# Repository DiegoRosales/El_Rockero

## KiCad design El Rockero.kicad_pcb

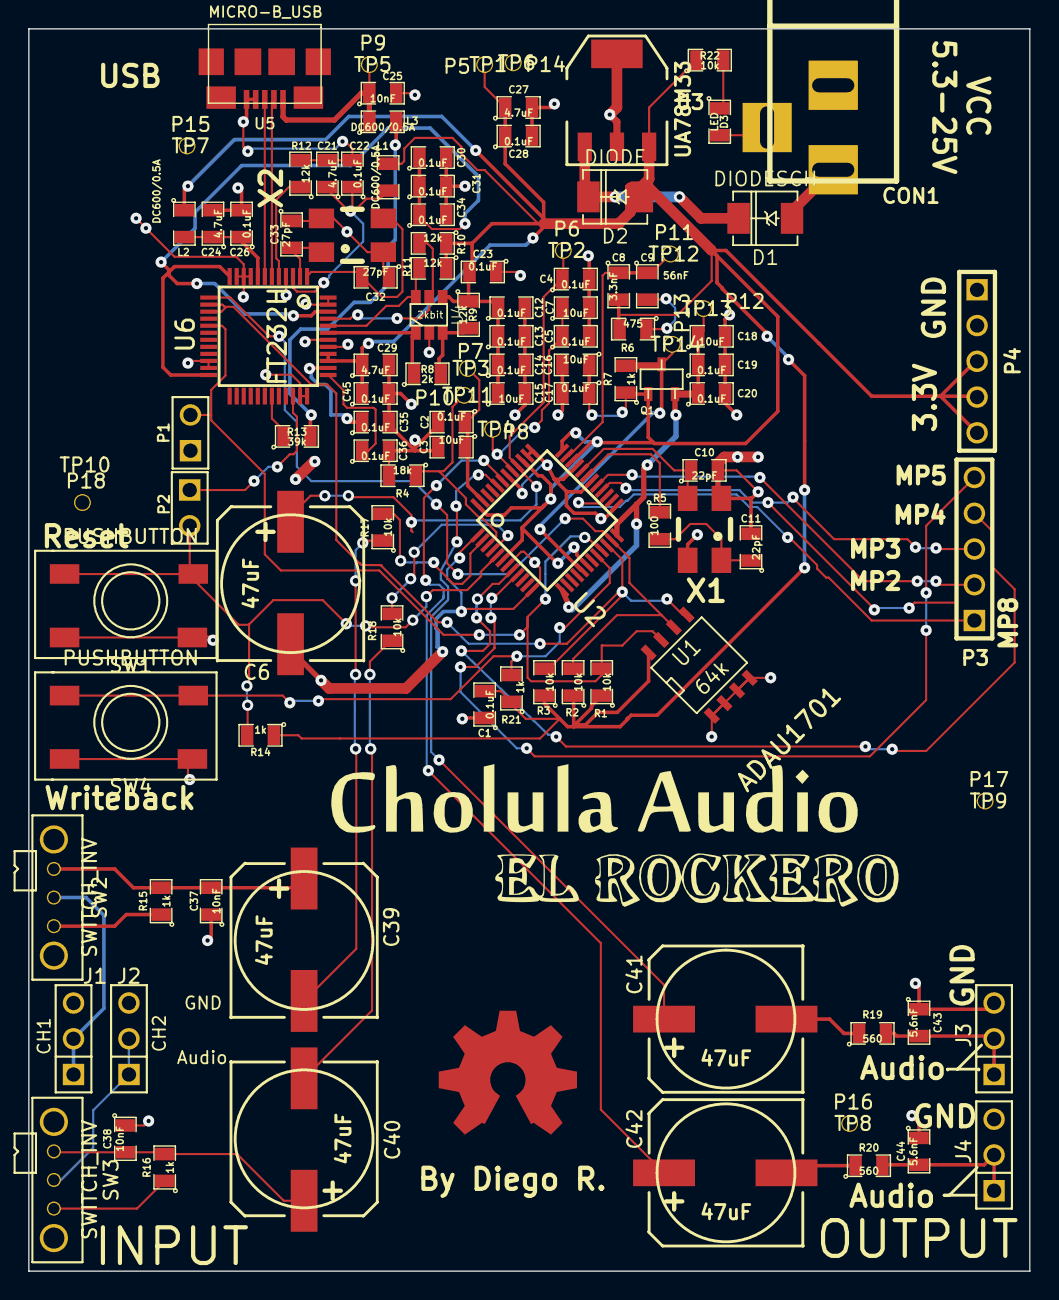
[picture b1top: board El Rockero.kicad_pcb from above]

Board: 2 copper layers, 71.1 x 88.3 mm, 110 parts (0 on the bottom side), 60 nets.

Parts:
C1, C2, C4, C5, C12, C13, C14, C17, C19, C20, C22, C23, C26, C28, C30, C31, C34, C35, C36, C45: 0.1uF; SM0805
C3, C7, C15, C16, C18: 10uF; SM0805
C6, C39, C40, C41, C42: 47uF; SMDSVP10
C8: 3.3nF; SM0805
C9: 56nF; SM0805
C10, C11: 22pF; SM0805
C21, C24, C27, C29: 4.7uF; SM0805
C25, C37, C38: 10nF; SM0805
C32, C33: 27pF; SM0805
C43, C44: 5.6nF; SM0805
CON1: BARREL_JACK
D1: DIODESCH; DO-214AC(SMA)
D2: DIODE; DO-214AC(SMA)
D3: LED; SM0805
J1: IN_L; PIN_ARRAY_3X1
J2: IN_R; PIN_ARRAY_3X1
J3: OUT_L; PIN_ARRAY_3X1
J4: OUT_R; PIN_ARRAY_3X1
L1, L2, L3: DC600/0.5A; SM0805
OSHW_COPPER_10MM: VAL**; OSHW_COPPER_10MM
P1: WP_Jumper; PIN_ARRAY_2X1
P2: USB_RST_JPR; PIN_ARRAY_2X1
P3, P4: CONN_5; PIN_ARRAY_5x1
P5: TP1; TP
P6: TP2; TP
P7: TP3; TP
P8: TP4; TP
P9: TP5; TP
P10: TP11; TP
P11: TP12; TP
P12: TP13; TP
P13: TP14; TP
P14: TP6; TP
P15: TP7; TP
P16: TP8; TP
P17: TP9; TP
P18: TP10; TP
Q1: ZXTP25040DFHTA; sot23
R1, R2, R3, R17, R18, R22: 10k; SM0805
R4: 18k; SM0805
R5: 100; SM0805
R6: 475; SM0805
R7, R14, R15, R16, R21: 1k; SM0805
R8: 2k; SM0805
R9, R10, R11, R12: 12k; SM0805
R13: 39k; SM0805
R19, R20: 560; SM0805
SW1, SW4: PUSHBUTTON
SW2, SW3: SWITCH_INV; SPDT Switch
U1: 64k; SO8N
U2: ADAU1701; LQFP48
U3: UA78M33
U4: 2kbit; SOT23_6
U5: MICRO-B_USB
U6: FT232H; LQFP48
X1, X2: CRYSTAL_4PIN; Crystal_SMD_0603_4Pads_RevA_09Aug2010

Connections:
+9V: CON1.1, D1.1
AVDD/PVDD (3.3v): C1.2, C8.2, C12.1, C13.1, C14.1, C15.1, C16.1, C17.1, C23.2, C27.1, C28.1, C29.1, C45.1, D2.1, L1.1, L2.1, P4.3, P4.4, P4.5, P5.1, Q1.1, R1.1, R2.1, R3.1, R6.2, R7.1, R9.1, R10.1, R11.1, R14.1, R21.1, R22.1, U1.8, U2.6, U2.18, U2.34, U2.36, U2.39, U2.48, U3.3, U4.4, U6.39, U6.40
DAC2: C41.1, U2.44
DAC3: C42.1, U2.43
DVDD: C18.1, C19.1, C20.1, P12.1, Q1.3, U2.13, U2.24
EECLK: R11.2, U4.6, U6.44
EECS: R10.2, U4.5, U6.45
EEDATA: R8.1, U4.1, U6.43
GND: C1.1, C2.2, C3.2, C4.2, C5.2, C6.2, C7.2, C10.2, C11.2, C12.2, C13.2, C14.2, C15.2, C16.2, C17.2, C18.2, C19.2, C20.2, C21.2, C22.2, C23.1, C24.2, C25.2, C26.2, C27.2, C28.2, C29.2, C30.2, C31.2, C32.1, C33.1, C34.2, C35.2, C36.2, C37.1, C38.1, C43.1, C44.1, C45.2, CON1.2, CON1.3, D3.2, J1.3, J2.3, J3.3, J4.3, P1.1, P4.1, P4.2, P14.1, P15.1, P16.1, P17.1, P18.1, R4.2, R12.2, SW1.1, SW1.2, SW4.1, SW4.2, U1.1, U1.2, U1.3, U1.4, U2.1, U2.7, U2.12, U2.25, U2.30, U2.33, U2.37, U2.38, U2.42, U3.2, U4.2, U5.4, U5.5, U6.4, U6.9, U6.10, U6.11, U6.22, U6.23, U6.35, U6.36, U6.41, U6.42, U6.47, U6.48, X1.2, X1.4, X2.2, X2.4
INF_L: R17.2, U2.2
INF_R: R18.2, U2.4
MP2: P3.2, U2.29
MP3: P3.3, U2.28
MP4: P3.4, U2.8
MP5: P3.5, U2.9
MP8: P3.1, U2.27
unnamed: R5.1, U2.31
unnamed: C9.2, R6.1
unnamed: C10.1, U2.32, X1.3
unnamed: C11.1, R5.2, X1.1
unnamed: D3.1, R22.2
unnamed: D1.2, D2.2, U3.1
unnamed: R13.1, U6.31
unnamed: C36.1, U6.37
unnamed: C32.2, U6.1, X2.3
unnamed: R12.1, U6.5
unnamed: U5.2, U6.6
unnamed: U5.3, U6.7
unnamed: P2.1, U6.34
unnamed: C33.2, U6.2, X2.1
unnamed: R8.2, R9.2, U4.3
unnamed: C42.2, R20.1
unnamed: C44.2, J4.1, J4.2, R20.2
unnamed: C41.2, R19.1
unnamed: C39.2, R17.1
unnamed: C37.2, C39.1, R15.2, SW2.1
unnamed: R15.1, SW2.3
unnamed: C38.2, C40.1, R16.2, SW3.1
unnamed: C43.2, J3.1, J3.2, R19.2
unnamed: R16.1, SW3.3
unnamed: C40.2, R18.1
unnamed: J2.1, J2.2, SW3.2
unnamed: J1.1, J1.2, SW2.2
RESET: P2.2, R14.2, SW1.3, SW1.4, U2.5
SCL: R2.2, U1.6, U2.23, U6.13
SDA: R3.2, U1.5, U2.22, U6.14, U6.15
TP2: C4.1, C6.1, P6.1, U2.40
TP3: C2.1, C3.1, P7.1, U2.47
TP4: C5.1, C7.1, P8.1, U2.41
TP5: C25.1, L3.1, P9.1, U5.1
TP11: P10.1, R4.1, U2.3
TP12: C8.1, C9.1, P11.1, U2.35
VBUS: L3.2, R13.2
VCCIO: C30.1, C31.1, C34.1, U6.12, U6.24, U6.46
VCORE: C35.1, U6.38
VDRIVE: P13.1, Q1.2, R7.2, U2.17
VPHY: C21.1, C22.1, L1.2, U6.3
VPLL: C24.1, C26.1, L2.2, U6.8
WB: R21.2, SW4.3, SW4.4, U2.20
WP: P1.2, R1.2, U1.7, U2.21, U6.17

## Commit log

2014-03-26 Added Files
    Added all the Files
